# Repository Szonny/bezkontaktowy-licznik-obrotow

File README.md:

# bezkontaktowy-licznik-obrotow
Projekt bezkontaktowego licznika obrotów, pozwalającego na wyznaczenie średnich parametrów liniowego ruchu obieku.

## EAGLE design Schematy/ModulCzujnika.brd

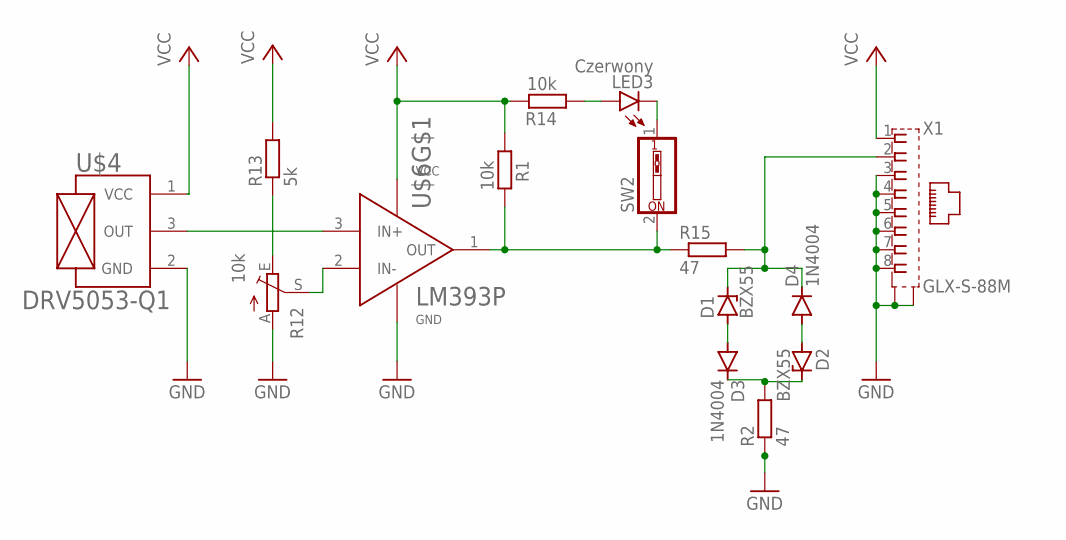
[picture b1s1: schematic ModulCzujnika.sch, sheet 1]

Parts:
D1, D2: BZX55; DO35Z10
D3, D4: 1N4004; DO41-10
LED3: Czerwony; LED5MM
R1, R14: 10k; 0207/7
R2, R15: 47; 0207/7
R12: 10k; CA6V
R13: 5k; 0207/7
SW2: SW_DIP-1; EDG-01
U$4: DRV5053-Q1; TO-92
U$6: LM393P; R-PDIP-T8
X1: GLX-S-88M

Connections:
GND: R2.1, R12.A, U$4.2 (GND), U$6.4 (GND), X1.3, X1.4, X1.5, X1.6, X1.7, X1.8, X1.S1, X1.S2
unnamed: D2.C, D3.C, R2.2
unnamed: D1.C, D4.C, R15.2, X1.2
unnamed: D2.A, D4.A
unnamed: D1.A, D3.A
unnamed: U$4.3 (OUT), U$6.3 (IN+)
unnamed: R12.S, U$6.2 (IN-)
unnamed: R1.2, R15.1, SW2.2, U$6.1 (OUT)
unnamed: R12.E, R13.1
unnamed: LED3.A, R14.1
unnamed: LED3.K (C), SW2.1
VCC: R1.1, R13.2, R14.2, U$4.1 (VCC), U$6.8 (VCC), X1.1

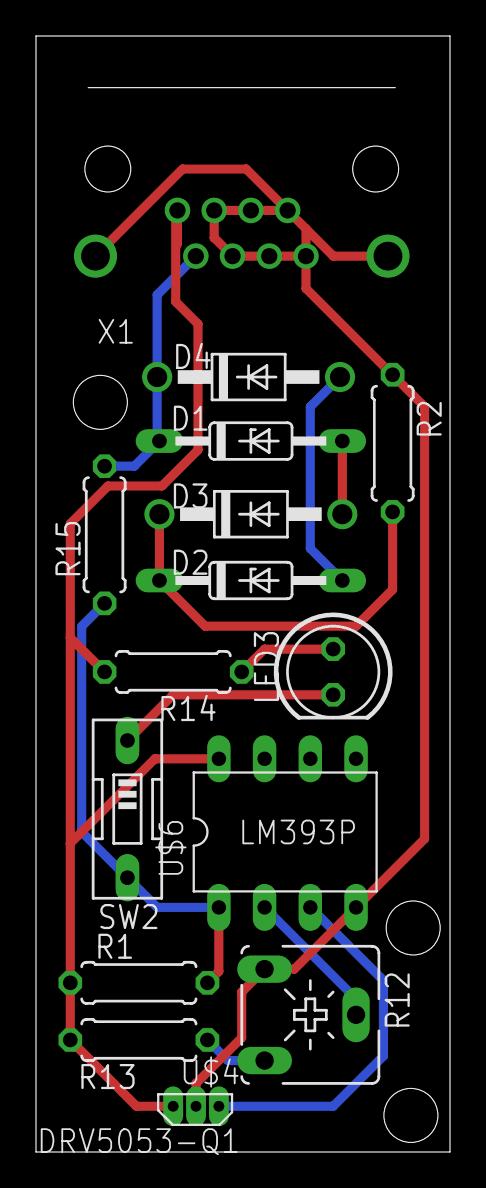
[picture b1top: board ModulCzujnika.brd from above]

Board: 2 copper layers, 23.0 x 62.0 mm, 15 parts (0 on the bottom side), 12 nets.

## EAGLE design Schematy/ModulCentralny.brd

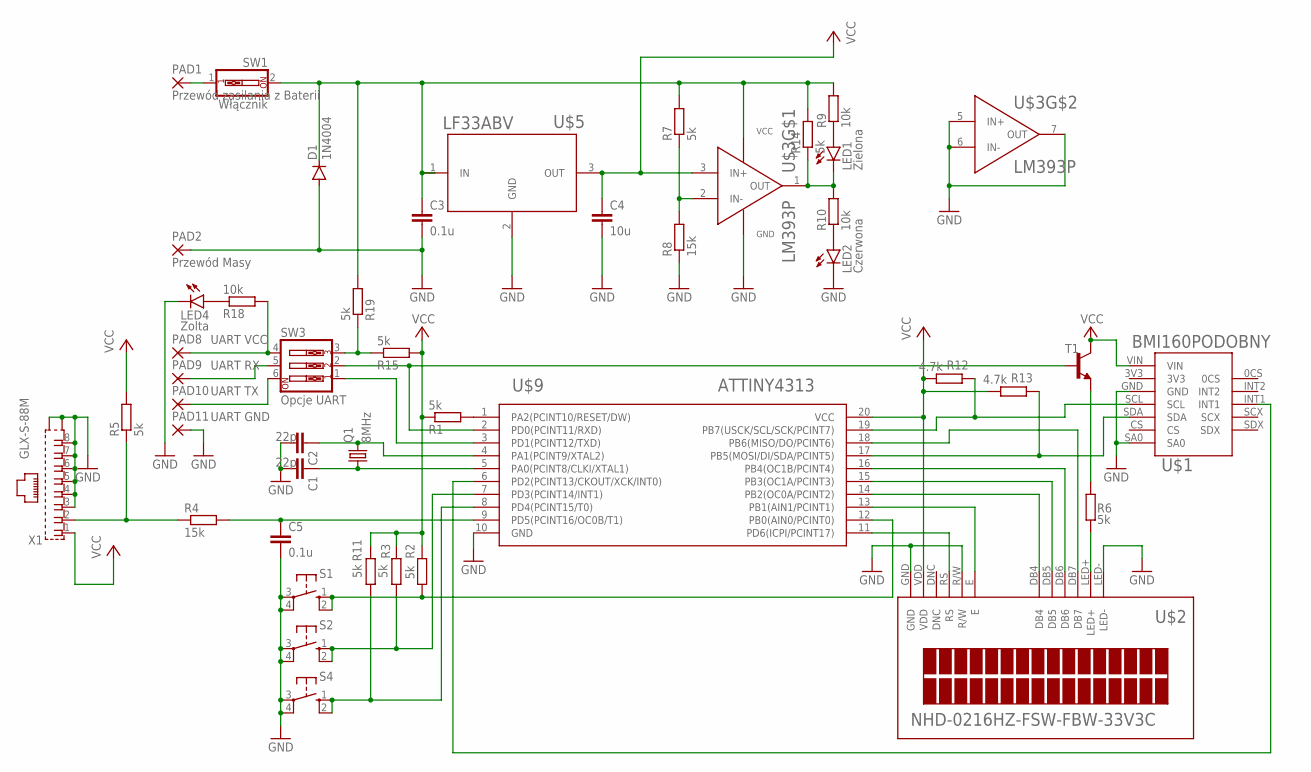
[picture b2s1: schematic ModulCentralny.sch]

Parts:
C1, C2: 22p; C2.5-3
C3, C5: 0.1u; C2.5-3
C4: 10u; C2.5-3
D1: 1N4004; DO41-10
LED1: Zielona; LED5MM
LED2: Czerwona; LED5MM
LED4: Zolta; LED5MM
PAD1: Przewód zasilania z Baterii; 2,54/1,1
PAD2: Przewód Masy; 2,54/1,1
PAD8: UART VCC; 3,17/1,3
PAD9: UART RX; 3,17/1,3
PAD10: UART TX; 3,17/1,3
PAD11: UART GND; 3,17/1,3
Q1: 8MHz; HC49U70
R1, R2, R3, R5, R6, R7, R11, R14, R15, R19: 5k; 0207/7
R4, R8: 15k; 0207/7
R9, R10, R18: 10k; 0207/7
R12, R13: 4.7k; 0207/7
S1, S2, S4: 10-XX; B3F-10XX
SW1: Włącznik; EDG-01
SW3: Opcje UART; EDG-03
T1: BC547B-NPN-TO92-CBE; TO92-CBE
U$1: BMI160PODOBNY; BMI160MODULE
U$2: NHD-0216HZ-FSW-FBW-33V3C
U$3: LM393P; R-PDIP-T8
U$5: LF33ABV; TO-220
U$9: ATTINY4313; 20P3
X1: GLX-S-88M

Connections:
GND: C1.2, C2.2, C3.2, C4.2, C5.2, D1.A, LED2.K (C), LED4.K (C), PAD2.1, PAD11.1, R8.1, S1.3, S1.4 (P1), S2.3, S2.4 (P1), S4.3, S4.4 (P1), U$1.GND, U$1.SA0, U$2.GND, U$2.LED-, U$2.R/W, U$3.4 (GND), U$3.5 (IN+), U$3.6 (IN-), U$3.7 (OUT), U$5.2 (GND), U$9.10 (GND), X1.3, X1.4, X1.5, X1.6, X1.7, X1.8, X1.S1, X1.S2
unnamed: R13.1, U$1.SDA, U$9.17 (PB5(MOSI/DI/SDA/PCINT5))
unnamed: C2.1, Q1.2, U$9.4 (PA1(PCINT9/XTAL2))
unnamed: R1.2, U$9.1 (PA2(PCINT10/RESET/DW))
unnamed: R11.1, S4.1 (S), S4.2 (S1), U$9.8 (PD4(PCINT15/T0))
unnamed: U$2.DB7, U$9.18 (PB6(MISO/DO/PCINT6))
unnamed: U$2.DB6, U$9.16 (PB4(OC1B/PCINT4))
unnamed: U$2.DB5, U$9.15 (PB3(OC1A/PCINT3))
unnamed: U$2.DB4, U$9.14 (PB2(OC0A/PCINT2))
unnamed: U$2.E, U$9.13 (PB1(AIN1/PCINT1))
unnamed: R4.1, R5.1, X1.2
unnamed: PAD1.1, SW1.1
unnamed: SW3.1, U$9.3 (PD1(PCINT12/TXD))
unnamed: SW3.2, T1.B, U$9.2 (PD0(PCINT11/RXD))
unnamed: R15.1, R19.1, SW3.3
unnamed: C1.1, Q1.1, U$9.5 (PA0(PCINT8/CLKI/XTAL1))
unnamed: R6.2, U$2.LED+
unnamed: C3.1, D1.C, R7.2, R9.2, R14.2, R19.2, SW1.2, U$3.8 (VCC), U$5.1 (IN)
unnamed: R12.1, U$1.SCL, U$9.19 (PB7(USCK/SCL/SCK/PCINT7))
unnamed: R7.1, R8.2, U$3.2 (IN-)
unnamed: LED1.K (C), R10.2, R14.1, U$3.1 (OUT)
unnamed: LED1.A, R9.1
unnamed: LED2.A, R10.1
unnamed: U$2.RS, U$9.11 (PD6(ICPI/PCINT17))
unnamed: U$1.INT1, U$9.6 (PD2(PCINT13/CKOUT/XCK/INT0))
unnamed: R6.1, T1.E
unnamed: C5.1, R4.2, U$9.9 (PD5(PCINT16/OC0B/T1))
unnamed: R3.1, S2.1 (S), S2.2 (S1), U$9.7 (PD3(PCINT14/INT1))
unnamed: R2.1, S1.1 (S), S1.2 (S1), U$9.12 (PB0(AIN0/PCINT0))
unnamed: PAD8.1, R18.2, SW3.4
unnamed: PAD10.1, SW3.6
unnamed: PAD9.1, SW3.5
unnamed: LED4.A, R18.1
VCC: C4.1, R1.1, R2.2, R3.2, R5.2, R11.2, R12.2, R13.2, R15.2, T1.C, U$1.VIN, U$2.VDD, U$3.3 (IN+), U$5.3 (OUT), U$9.20 (VCC), X1.1

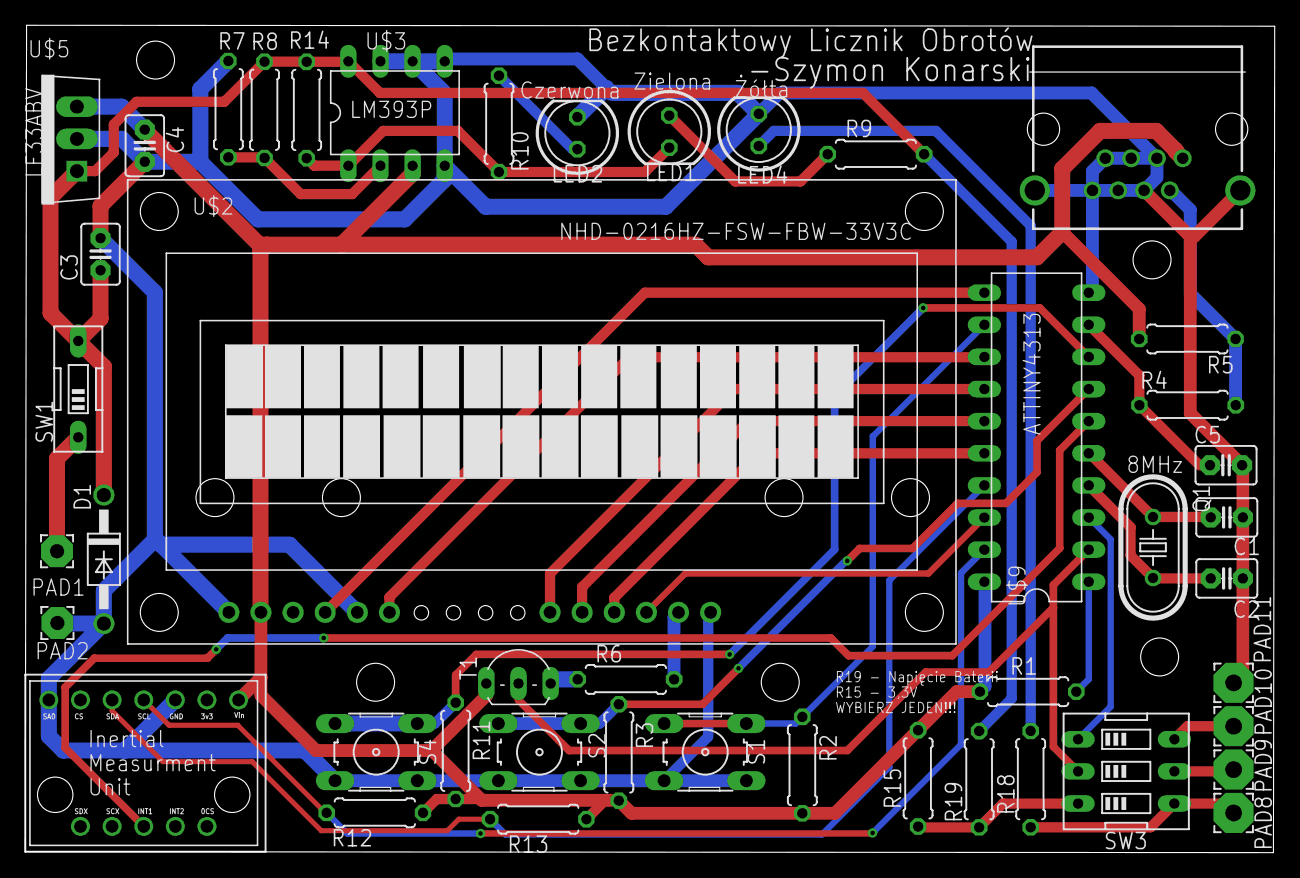
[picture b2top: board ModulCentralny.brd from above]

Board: 2 copper layers, 98.8 x 65.4 mm, 45 parts (1 on the bottom side), 34 nets.

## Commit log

2025-11-12 Pierwsze schematy prototypu
    Schematy obrazujące pierwsze pomysły na szczegółową konstrukcje urządzenia
2025-11-12 Pliki schematow po poprawkach
    Pliki schematów po naniesieniu poprawek zasugerowanych podczas zajęć.
    Kompletny schemat fizyczny płytki modułu czujnika.
2025-12-10 Dodanie podciągającego rezystora na wyjście lm393
2025-12-10 Poprawione pdf ze schematami
2026-01-17 Nowa płytka w wymiarach 6,6x9,9mm
2026-03-20 Program główny, obsługa I/O, 4 tryby pracy
2026-03-20 Częściowe zabezpieczenie modułu czujnika
    Częściowe zabezpieczenie modułu czujnika przed nagłym wzrostem napięcia na wejściu modułu.
2026-03-20 Aktualizacja listy Komponentów
    Dodanie tranzystora do możliwości wygaszenia podświetlenia wyświetlacza
